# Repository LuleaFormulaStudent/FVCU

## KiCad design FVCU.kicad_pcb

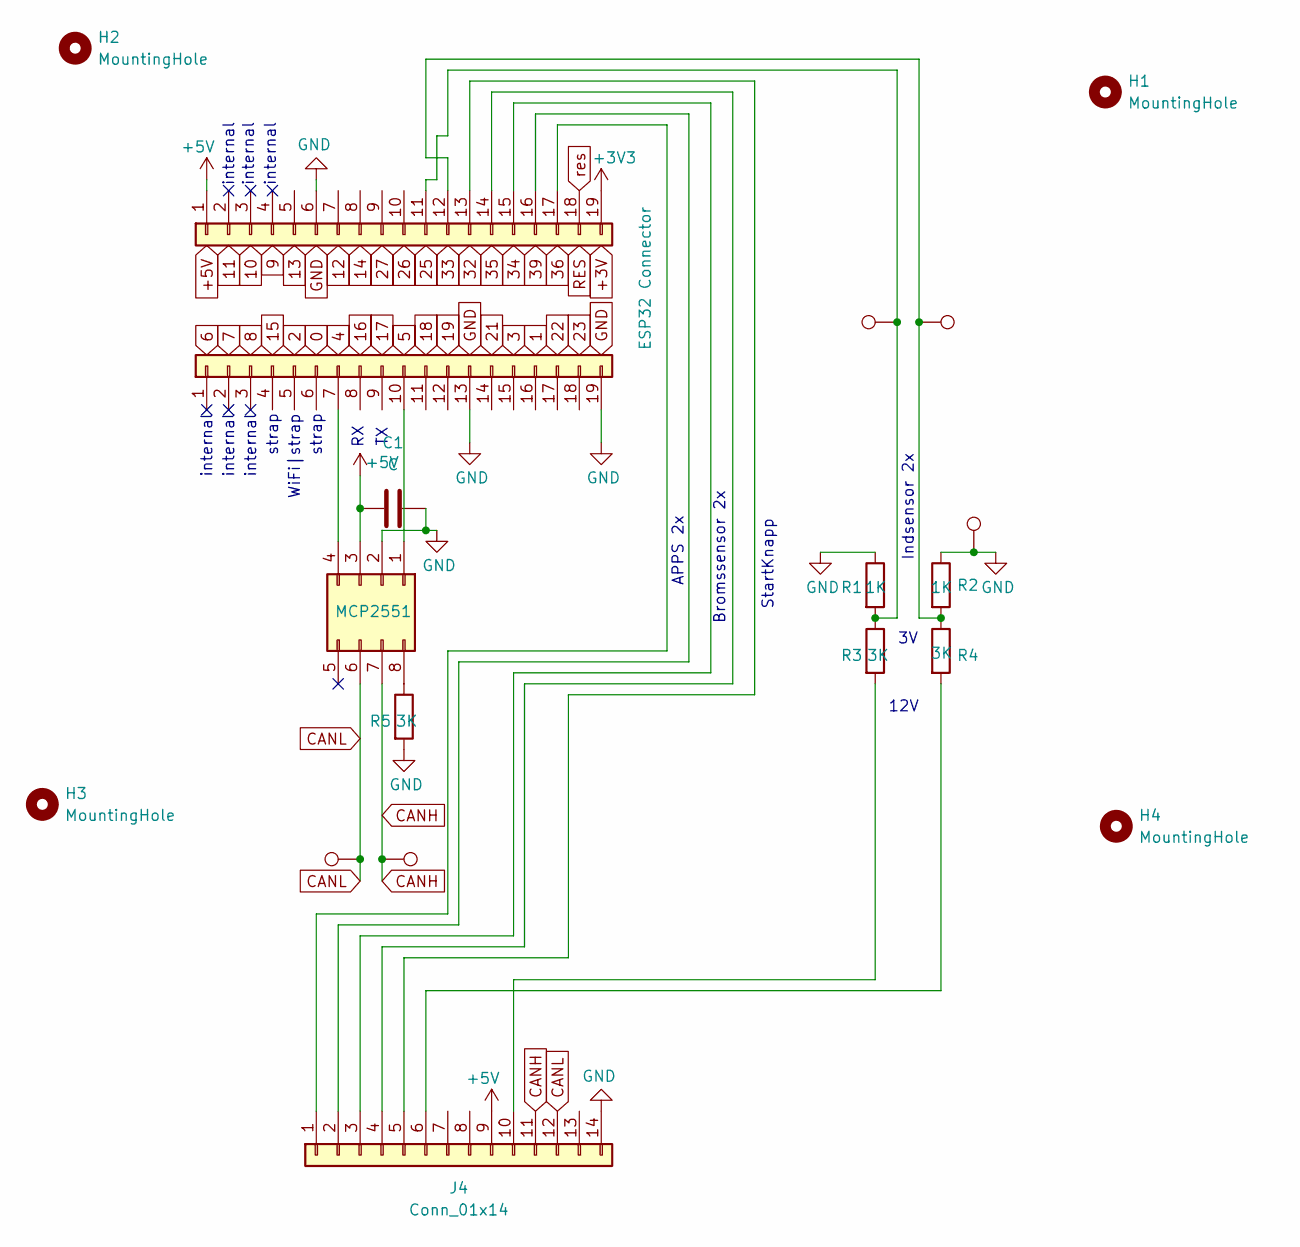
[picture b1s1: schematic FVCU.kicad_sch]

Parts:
C1: C; C_0805_2012Metric_Pad1.18x1.45mm_HandSolder
H1, H2, H3, H4: MountingHole; MountingHole_3.2mm_M3
J1: ESP32 Connector; PinSocket_1x19_P2.54mm_Vertical
J2: Conn_01x19; PinSocket_1x19_P2.54mm_Vertical
J3: MCP2551
J4: Conn_01x14; TE_776267-1
R1, R2: 1K; R_0805_2012Metric
R3, R4, R5: 3K; R_0805_2012Metric
TP1, TP2, TP3, TP4, TP5: TestPoint; TestPoint_Pad_D2.0mm

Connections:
+3V3: J2.19
+5V: C1.1, J2.1, J3.3, J4.9
CANH: J3.7, J4.11, TP2.1
CANL: J3.6, J4.12, TP1.1
GND: C1.2, J1.13, J1.19, J2.6, J3.2, J4.14, R1.1, R2.1, R5.2, TP3.1
unnamed: J1.7, J3.4
unnamed: J1.10, J3.1
unnamed: J2.11, R1.2, R3.1, TP4.1
unnamed: J2.12, R2.2, R4.1, TP5.1
unnamed: J2.13, J4.5
unnamed: J2.14, J4.4
unnamed: J2.15, J4.3
unnamed: J2.16, J4.2
unnamed: J2.17, J4.1
unnamed: J3.8, R5.1
unnamed: J4.6, R4.2
unnamed: J4.10, R3.2
res: J2.18

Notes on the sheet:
internal
12V
strap
StartKnapp
Bromssensor 2x
WiFi|strap
APPS 2x
Indsensor 2x

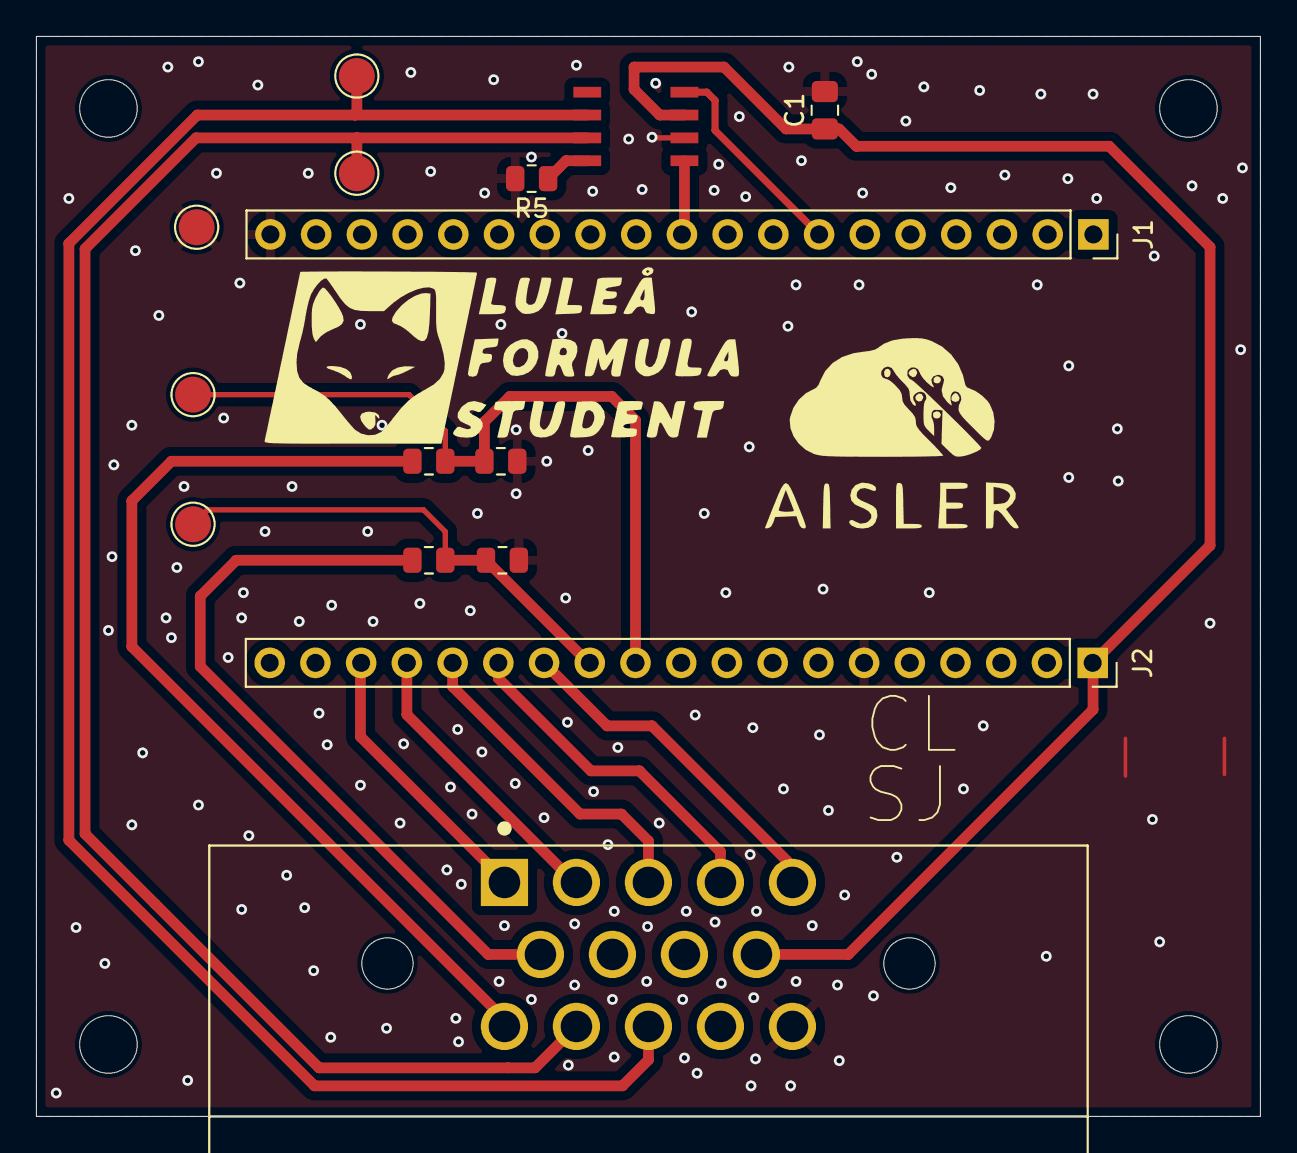
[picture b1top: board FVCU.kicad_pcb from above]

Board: 2 copper layers, 68.0 x 60.0 mm, 19 parts (0 on the bottom side), 16 nets.

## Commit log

2025-04-12 InitialCommit
    InitialCommit
2025-04-12 Init_commit
2025-04-12 Mjau
    Mjau
2026-04-26 make sure it's all up to date before update
